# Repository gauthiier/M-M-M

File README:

WORK IN PROGRESS...
Motors & Music & Motions (M&M&M)
dviid, bill verplank, jakob bak

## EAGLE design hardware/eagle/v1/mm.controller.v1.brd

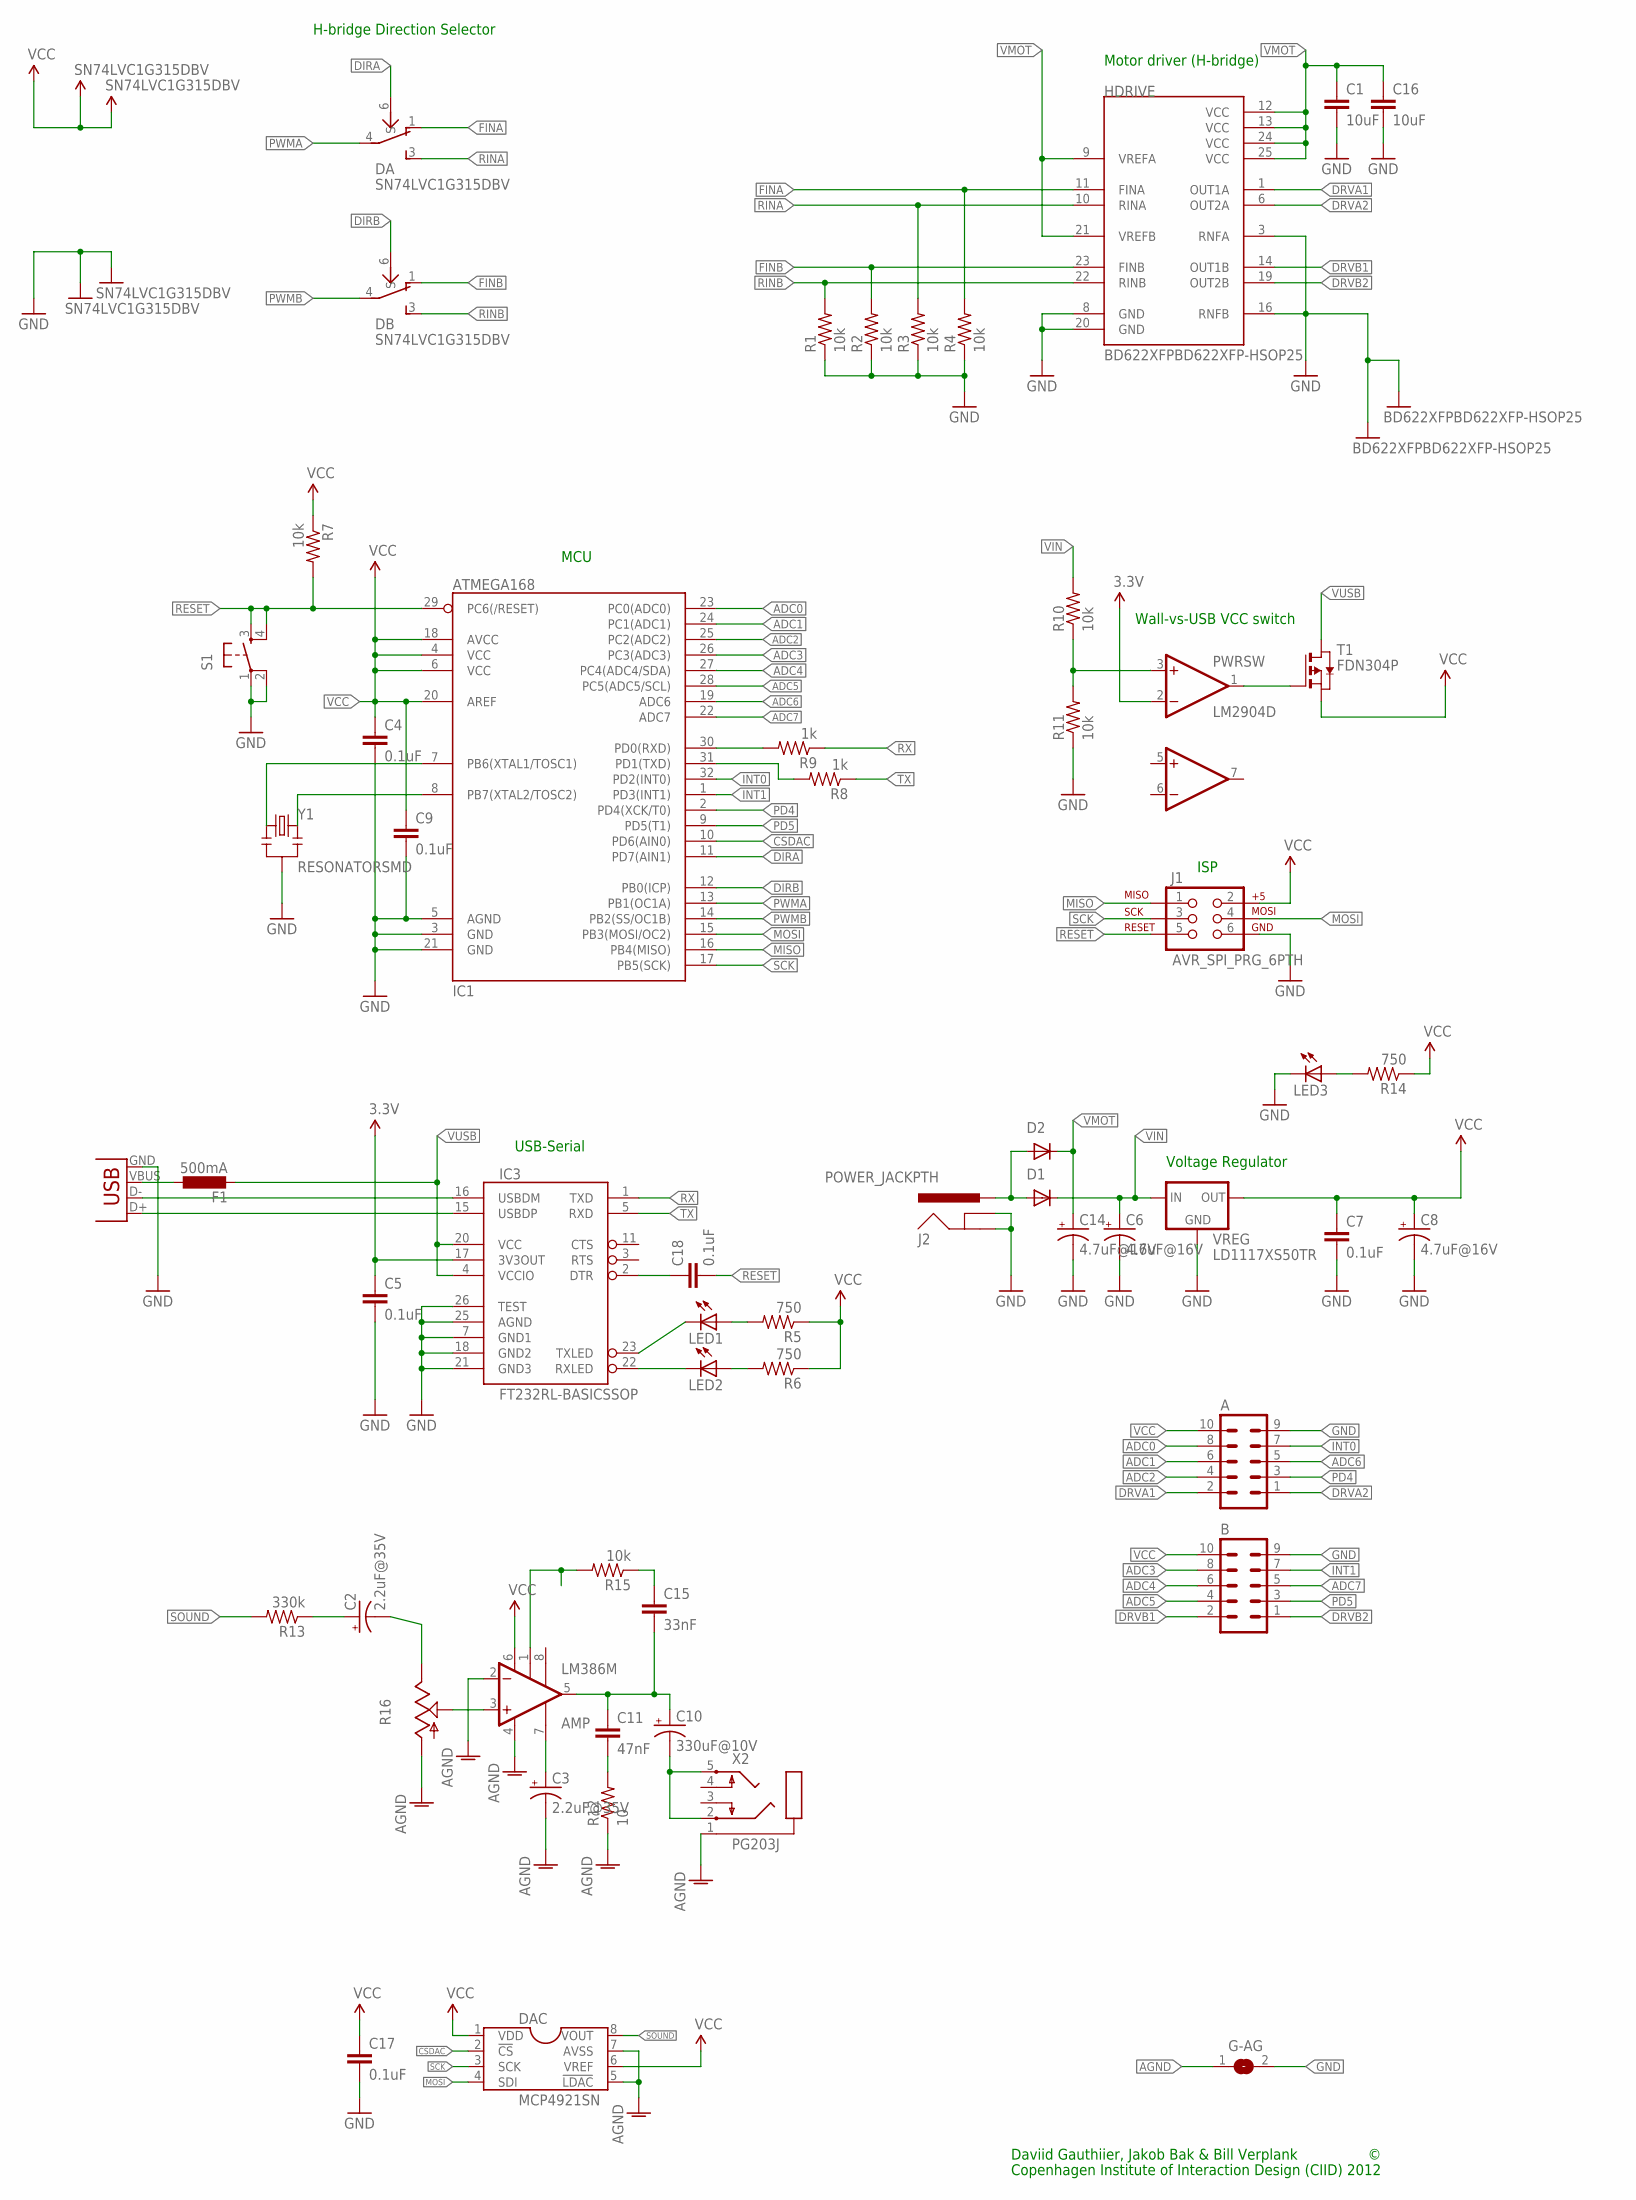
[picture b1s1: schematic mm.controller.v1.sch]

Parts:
A: ML10
AMP: LM386M; SOIC8
B: ML10
C1, C16: 10uF; 0805
C2, C3: 2.2uF@35V; PANASONIC_B
C4, C5, C7, C9, C17, C18: 0.1uF; 0805
C6, C8, C14: 4.7uF@16V; PANASONIC_B
C10: 330uF@10V; PANASONIC_F
C11: 47nF; 0805
C15: 33nF; 0805
D1, D2: DIODESMB; SMB-DIODE
DA: SN74LVC1G315DBV; SOT23-6
DAC: MCP4921SN; SOIC8
DB: SN74LVC1G315DBV; SOT23-6
F1: 500mA; L1812
G-AG: SJ
HDRIVE: BD622XFPBD622XFP-HSOP25; HSOP25
IC1: ATMEGA168; TQFP32-08
IC3: FT232RL-BASICSSOP; SSOP28DB
J1: AVR_SPI_PRG_6PTH; 2X3
J2: POWER_JACKPTH; POWER_JACK_PTH
LED1, LED2, LED3: LED1206; LED-1206
PWRSW: LM2904D; SOIC8
R1, R2, R3, R4, R7, R10, R11, R15: 10k; 0805
R5, R6, R14: 750; 0805
R8, R9: 1k; 0805
R12: 10; 0805
R13: 330k; 0805
R16: TRIM_US-PT10; PT-10
S1: TAC_SWITCHSMD; TACTILE_SWITCH_SMD
T1: FDN304P; SOT-23
VREG: LD1117XS50TR; SOT223
X1: USB-SMD-NS; USB-MINIB-NOSTOP
X2: PG203J
Y1: RESONATORSMD; RESONATOR-SMD

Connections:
3.3V: C5.1, IC3.17 (3V3OUT), PWRSW.2 (-INA)
ADC0: A.8, IC1.23 (PC0(ADC0))
ADC1: A.6, IC1.24 (PC1(ADC1))
ADC2: A.4, IC1.25 (PC2(ADC2))
ADC3: B.8, IC1.26 (PC3(ADC3))
ADC4: B.6, IC1.27 (PC4(ADC4/SDA))
ADC5: B.4, IC1.28 (PC5(ADC5/SCL))
ADC6: A.5, IC1.19 (ADC6)
ADC7: B.5, IC1.22 (ADC7)
AGND: AMP.2 (-IN), AMP.4 (V-), C3.-, DAC.5 (!LDAC), DAC.7 (AVSS), G-AG.1, R12.1, R16.A, X2.1
CSDAC: DAC.2 (!CS), IC1.10 (PD6(AIN0))
DIRA: DA.6 (S), IC1.11 (PD7(AIN1))
DIRB: DB.6 (S), IC1.12 (PB0(ICP))
DRVA1: A.2, HDRIVE.1 (OUT1A)
DRVA2: A.1, HDRIVE.6 (OUT2A)
DRVB1: B.2, HDRIVE.14 (OUT1B)
DRVB2: B.1, HDRIVE.19 (OUT2B)
FINA: DA.1 (INA), HDRIVE.11 (FINA), R4.2
FINB: DB.1 (INA), HDRIVE.23 (FINB), R2.2
GND: A.9, B.9, C1.2, C4.2, C5.2, C6.-, C7.2, C8.-, C9.2, C14.-, C16.2, C17.2, DA.2 (GND), DB.2 (GND), G-AG.2, HDRIVE.3 (RNFA), HDRIVE.8 (GND), HDRIVE.16 (RNFB), HDRIVE.20 (GND), HDRIVE.GND@1 (GND), HDRIVE.GND@2 (GND), IC1.3 (GND), IC1.5 (AGND), IC1.21 (GND), IC3.7 (GND1), IC3.18 (GND2), IC3.21 (GND3), IC3.25 (AGND), IC3.26 (TEST), J1.6, J2.GND, J2.GNDBREAK, LED3.C, PWRSW.4 (GND), R1.1, R2.1, R3.1, R4.1, R11.1, S1.1, S1.2, VREG.1 (GND), X1.GND, Y1.2
INT0: A.7, IC1.32 (PD2(INT0))
INT1: B.7, IC1.1 (PD3(INT1))
MISO: IC1.16 (PB4(MISO)), J1.1
MOSI: DAC.4 (SDI), IC1.15 (PB3(MOSI/OC2)), J1.4
unnamed: IC1.7 (PB6(XTAL1/TOSC1)), Y1.1
unnamed: IC1.8 (PB7(XTAL2/TOSC2)), Y1.3
unnamed: IC3.16 (USBDM), X1.D-
unnamed: IC3.15 (USBDP), X1.D+
unnamed: IC3.23 (TXLED), LED1.C
unnamed: IC3.22 (RXLED), LED2.C
unnamed: LED1.A, R5.2
unnamed: LED2.A, R6.2
unnamed: F1.1, X1.VBUS
unnamed: IC1.30 (PD0(RXD)), R9.2
unnamed: IC1.31 (PD1(TXD)), R8.2
unnamed: AMP.3 (+IN), R16.S
unnamed: PWRSW.3 (+INA), R10.1, R11.2
unnamed: PWRSW.1 (OUTA), T1.3 (G)
unnamed: LED3.A, R14.2
unnamed: C18.1, IC3.2 (DTR)
unnamed: C2.+, R13.1
unnamed: AMP.5 (OUT), C10.+, C11.1, C15.2
unnamed: C10.-, X2.2, X2.5
unnamed: C11.2, R12.2
unnamed: C15.1, R15.1
unnamed: AMP.1 (G1), R15.2
unnamed: AMP.7 (BYPASS), C3.+
PD4: A.3, IC1.2 (PD4(XCK/T0))
PD5: B.3, IC1.9 (PD5(T1))
PWMA: DA.4 (OUT), IC1.13 (PB1(OC1A))
PWMB: DB.4 (OUT), IC1.14 (PB2(SS/OC1B))
RESET: C18.2, IC1.29 (PC6(/RESET)), J1.5, R7.2, S1.3, S1.4
RINA: DA.3 (INB), HDRIVE.10 (RINA), R3.2
RINB: DB.3 (INB), HDRIVE.22 (RINB), R1.2
RX: IC3.1 (TXD), R9.1
SCK: DAC.3 (SCK), IC1.17 (PB5(SCK)), J1.3
SIN: C2.-, R16.E
SOUND: DAC.8 (VOUT), R13.2
TX: IC3.5 (RXD), R8.1
VCC: A.10, AMP.6 (V+), B.10, C4.1, C7.1, C8.+, C9.1, C17.1, DA.5 (VCC), DAC.1 (VDD), DAC.6 (VREF), DB.5 (VCC), IC1.4 (VCC), IC1.6 (VCC), IC1.18 (AVCC), IC1.20 (AREF), J1.2, PWRSW.8 (VCC), R5.1, R6.1, R7.1, R14.1, T1.2 (S), VREG.2 (OUT)
VIN: C6.+, D1.C, R10.2, VREG.3 (IN)
VMOT: C1.1, C14.+, C16.1, D2.C, HDRIVE.9 (VREFA), HDRIVE.12 (VCC), HDRIVE.13 (VCC), HDRIVE.21 (VREFB), HDRIVE.24 (VCC), HDRIVE.25 (VCC)
VUSB: F1.2, IC3.4 (VCCIO), IC3.20 (VCC), T1.1 (D)
VWALL: D1.A, D2.A, J2.PWR

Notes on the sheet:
Daviid Gauthiier, Jakob Bak & Bill Verplank
Copenhagen Institute of Interaction Design (CIID) 2012
USB-Serial
Voltage Regulator
Wall-vs-USB VCC switch
ISP
MCU
Motor driver (H-bridge)
H-bridge Direction Selector

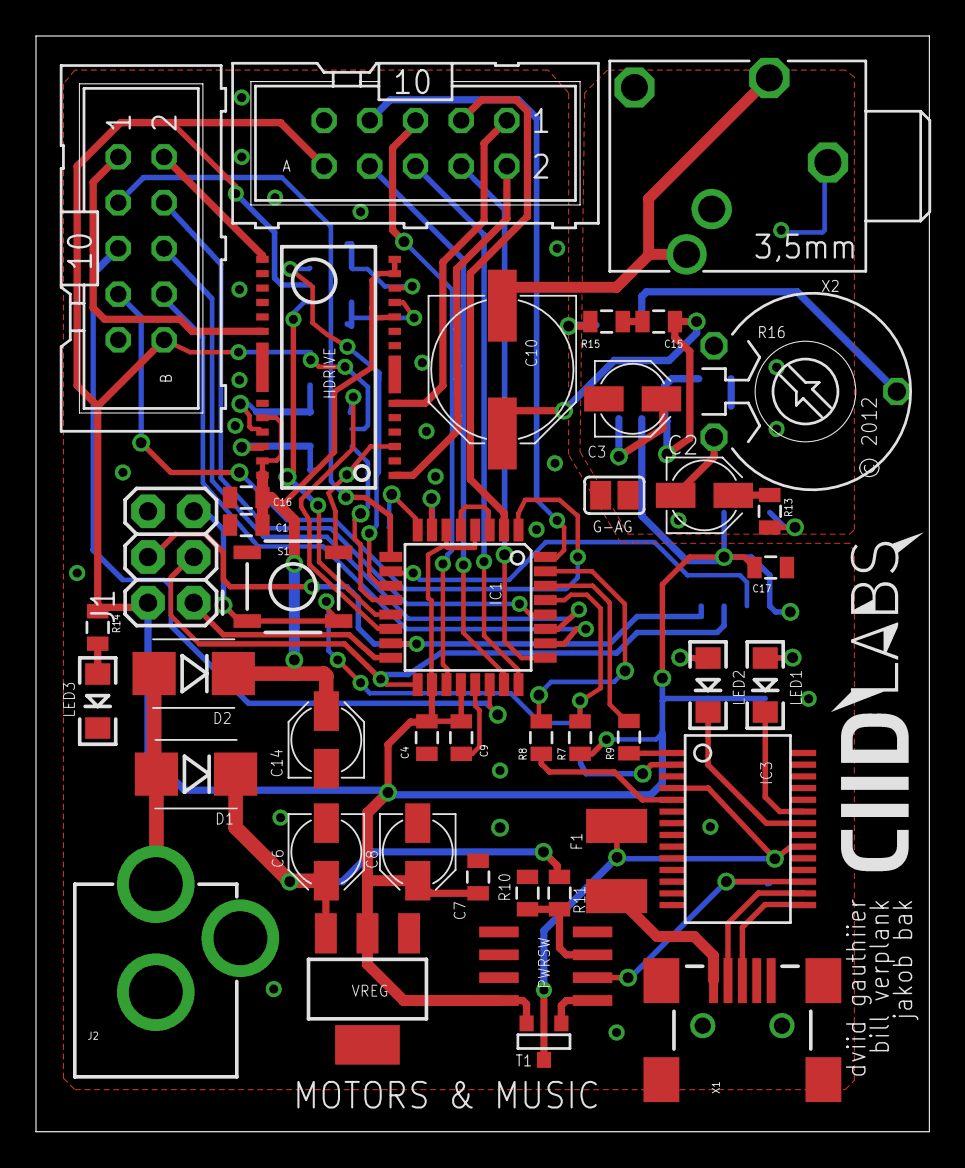
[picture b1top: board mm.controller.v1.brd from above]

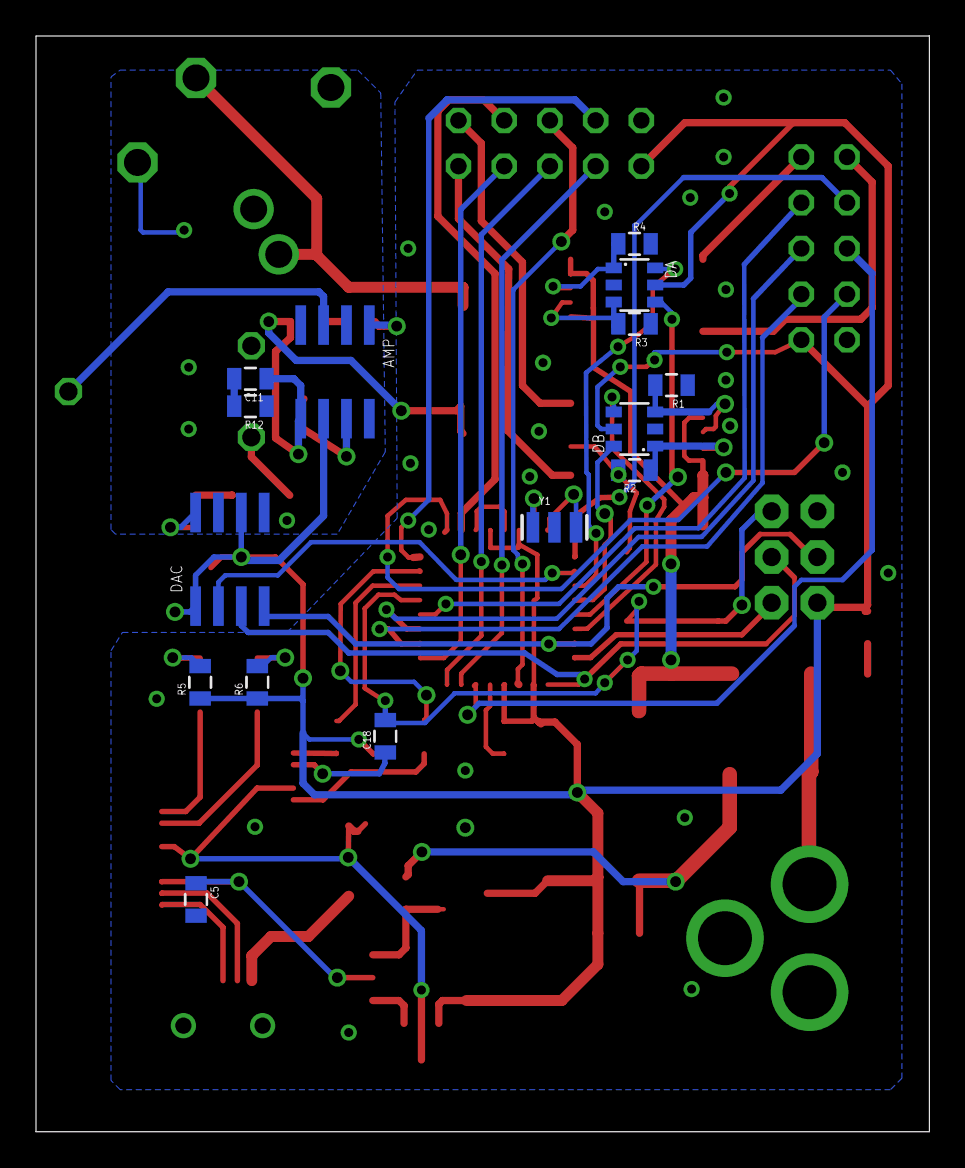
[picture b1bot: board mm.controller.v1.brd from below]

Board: 2 copper layers, 49.6 x 60.9 mm, 58 parts (15 on the bottom side), 64 nets.

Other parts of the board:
U$2: CIID-LABS-LOGO

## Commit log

2012-11-03 HAHA!
2012-11-04 DampSpringMass code
    none works yet - having trouble with velocity estimation.
2012-11-05 Fixed MMM library directory structure
2012-11-05 Motion examples and tests
2012-11-11 Lots of minor tweeks. Primarily changing wavetable to 8bit with 16 different waveforms
2012-11-26 Added Motion lib 101
2012-12-06 Update Motion library and added an example how-to in apps folder
2012-12-07 Getting Synched
    First time after a lot of tries. -Bill
2012-12-07 edited GitHowTo
    lines 4 and 20
2012-12-07 hmmmmm
2013-01-11 cleaning up
2013-01-23 New motion lib
2013-01-23 wednesday commit
2013-01-23 Oscillator selects and examples
    Made it possible to select type and number of oscillators to compile
    (via preprocessor). Made Examples folder to library where tutorials
    will go in.
2013-01-24 Added some comment text for interrupt select and NUM_OSCILLATORS
2013-01-24 Thursday Commit
    including David's lib from yesterday
2013-01-24 Bills Pendulum Works!
2013-01-24 Bill - Pendulum and PendulumDamped
2013-01-24 Bill's Protocol Pendulum Plot
    Added force-out to pendulum
2013-01-24 Changes to Motion, Motor and Music Library
    Motion library still needs to be fixed. Don't use yet.
2013-01-25 bill friday
2013-01-25 created new center example
2013-01-25 Jakob changed some comments on bill's computer
2013-01-28 Updates: Motion + Motor
    Integration with unsyncable branch
2013-01-28 Added Oscilloscope code in apps
2013-01-29 Bill's Music mess
2013-01-29 Slight fixes to motion and music library
2013-01-30 Changes to Music.h and Music.cpp
2013-01-30 Revert "Changes to Music.h and Music.cpp"
    This reverts commit 8b24803aa2fd9792ec9507376fc52fd238742b00.
2013-01-30 Fixed Motion
2013-01-30 Updated Music
2013-01-30 Updates to Music.h, deleted Midi.h and Midi.cpp
    We can now use these commands in the arduino sketch:
    #define NUM_OSCILLATORS x // where x is 1, 2 or 3
    #define BIT_DEPTH x // where x is 8 or 12
    Deleted Midi library files as they where causing multiple definition
    errors with the outdated Music.h file.
2013-02-01 Changed default direction for MOTORB
    Due to hardware design of MM board MOTORA and MOTORB had opposite
    directions. Fixed by switching settings for MOTORB in
    MMotor::direction(DIRECTION) function
2013-02-05 Updated Music.h and added MIDI functionality to it
2013-02-05 Added placeholders for tutorial library
2013-02-05 KEYWORD1
    Moror
2013-02-05 Pulse_Beat.ino
    added to software/lib/MMM/examples/motor/
2013-02-05 Added Motion update_position
2013-02-05 Bill Examples
    M&MStudioBV
2013-02-09 Added ForceProfile
2013-02-09 Updated sketches for TEI workshop
2013-02-10 TEI Studio
2013-02-10 Added examples
2013-02-10 Added more examples
2013-02-10 Added Music examples to Apps folder
2013-02-10 updated keywords
2013-03-15 Fixed small screen issues
2013-03-18 Goldsmiths
2013-03-21 Updated _8_mid.ino
2013-05-15 Changes to Music.h and keywords.txt
    added support for the miniCFO platform to work with the audio
2013-05-15 added reference for the Music library to examples folder
2013-05-15 Added Music Controls processing sketch to processing folder
2013-05-21 Added FM synthesis and corrected detune via MIDI
2013-05-21 small changes to FM part, added MIDI CC for FM2
2013-05-21 updated library documentation Arduino "sketch"
2013-05-21 updated music library documentation sketch and keywords
2013-05-21 Added example sketch for FM synthesis
2013-05-21 getting FM
2013-05-22 fixed _8_FM.ino Arduino sketch
    A conflict in github added some lines of text to the sketch that would
    prevent it from compiling
2013-06-06 Fixed? a problem with MIDI when running Processing sketch Music_Controls and playing notes from sequencer program (like Ableton Live) at the same time.
2013-09-26 Added pdf of board layout
2013-09-26 Made some fixes to the MIDI processing sketch and MIDI example
2013-09-27 Processing sketch Music_Controls_4.pde now shows actual values in the Processing terminal

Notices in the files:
hardware/eagle/v1/mm.controller.v1.brd:
© 2012
